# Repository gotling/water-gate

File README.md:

# Watergate

A growhose helper. Sensors and watering of plants with added nutrition. 

# Configuration

WiFi config set using WiFi Manager by connecting to network Watergate on first boot.

**gmtOffset_sec**

Adjustment in seconds from GMT

**waterHour**

Array of hours when automatic watering should be done

## MQTT

Setup to use Adafruit IO service.

Configure username, password and topic by creating a *config.h* file with the following defines:

    #define MQTT_USER ""
    #define MQTT_PASSWORD ""
    #define MQTT_TOPIC ""

# Hardware

ESP32 devkit.

DHT22 temperature and humidity sensor.

12v AGM battery.

12v 5w water pump.

Hygrometers for measuring soil humidity.

Buck converter for getting 5v from 12v battery.

Simple voltage divider for checking battery level.

MOSFETs for controlling pump, motor and sensors.

Water level sensors.

# Schematics

First time using KiCad to help with construction.

# Software

Written in Arduino IDE 2.0.

Coded in C.

# Enclosures

Made in Fusion 360 with main purpouse to protect electronics from direct sunligt.

https://a360.co/3csUwN7

# Libraries

These libraries needs to be installed in Arduino IDE to be able to build.

**FTDebouncer** by Ubi de Feo

https://github.com/ubidefeo/FTDebouncer

**DHT sensor library** by Adafruit

https://github.com/adafruit/DHT-sensor-library

**WiFiManager** by tzapu

https://github.com/tzapu/WiFiManager

**PubSubClient** by Nick O'Leary

https://github.com/knolleary/pubsubclient

**DallasTemperature** by Miles Burton

https://github.com/milesburton/Arduino-Temperature-Control-Library

**OneWire** by Jim Studt, ...

https://www.pjrc.com/teensy/td_libs_OneWire.html

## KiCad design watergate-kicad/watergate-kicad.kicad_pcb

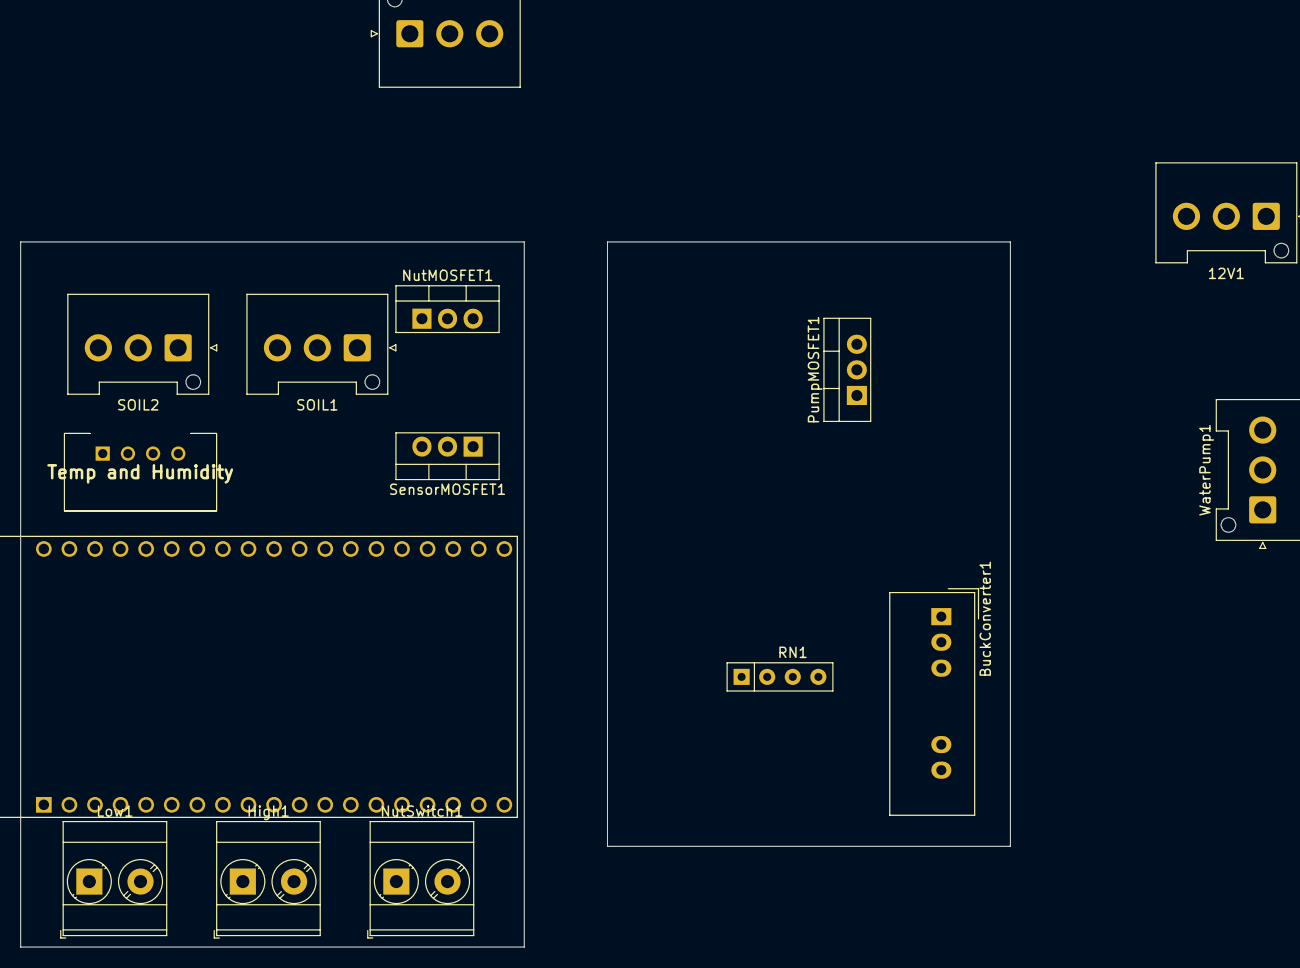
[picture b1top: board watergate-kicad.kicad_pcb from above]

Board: 2 copper layers, 98.3 x 70.0 mm, 15 parts (0 on the bottom side), 18 nets, no tracks yet.

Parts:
12V1: Battery; JST_VH_B3P-VH-FB-B_1x03_P3.96mm_Vertical
BuckConverter1: DC12V-DC5V; Converter_DCDC_Murata_NCS1SxxxxSC_THT
High1: WaterLevelSwitch; TerminalBlock_Phoenix_MKDS-3-2-5.08_1x02_P5.08mm_Horizontal
Low1: WaterLevelSwitch; TerminalBlock_Phoenix_MKDS-3-2-5.08_1x02_P5.08mm_Horizontal
NutMOSFET1: IRLZ34N; TO-220-3_Vertical
NutMotor1: Motor_DC; JST_VH_B3P-VH-FB-B_1x03_P3.96mm_Vertical
NutSwitch1: Switch; TerminalBlock_Phoenix_MKDS-3-2-5.08_1x02_P5.08mm_Horizontal
PumpMOSFET1: IRLZ34N; TO-220-3_Vertical
RN1: VoltageDivider; R_Array_SIP4
SOIL1, SOIL2: Soil_Measure_Analog; JST_VH_B3P-VH-FB-B_1x03_P3.96mm_Vertical
SensorMOSFET1: IRLZ34N; TO-220-3_Vertical
Temp and Humidity: DHT22
U1: ESP32-DEVKITC-32D; MODULE_ESP32-DEVKITC-32D
WaterPump1: Motor_DC; JST_VH_B3P-VH-FB-B_1x03_P3.96mm_Vertical

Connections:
unnamed: 12V1.1 (+), BuckConverter1.2 (+VIN), RN1.3, WaterPump1.1 (+)
unnamed: 12V1.2 (-), BuckConverter1.1 (-VIN), NutMOSFET1.2 (D), PumpMOSFET1.2 (D), RN1.1, U1.14 (GND1)
unnamed: High1.1, Low1.1, NutSwitch1.1, Temp and Humidity.1 (VDD), U1.1 (3V3)
unnamed: NutMOSFET1.1 (G), NutMotor1.2 (-)
unnamed: NutMOSFET1.3 (S), U1.13 (IO12)
unnamed: BuckConverter1.6 (+VOUT), NutMotor1.1 (+), SOIL1.2 (VCC), SOIL2.2 (VCC), U1.19 (EXT_5V)
unnamed: PumpMOSFET1.1 (G), WaterPump1.2 (-)
unnamed: PumpMOSFET1.3 (S), U1.12 (IO14)
unnamed: SOIL1.1 (GND), SOIL2.1 (GND), SensorMOSFET1.1 (G)
unnamed: SOIL1.3 (AUOT), U1.31 (IO16)
unnamed: SOIL2.3 (AUOT), U1.32 (IO4)
unnamed: SensorMOSFET1.2 (D), Temp and Humidity.4 (GND), U1.20 (GND3)
unnamed: SensorMOSFET1.3 (S), U1.33 (IO0)
unnamed: High1.2, U1.9 (IO25)
unnamed: Low1.2, U1.10 (IO26)
unnamed: NutSwitch1.2, U1.11 (IO27)
unnamed: RN1.2, U1.15 (IO13)
unnamed: Temp and Humidity.2 (DATA), U1.21 (IO23)

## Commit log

2022-06-16 Add liquid level sensors
2022-06-16 Add 3 hygrometer sensors and one temperature probe
2022-06-30 Read battery voltage
2022-06-30 Wiring hints
2022-06-30 Add nutrition until target
2022-06-30 Button and LED form manual control
2022-07-15 MQTT, automation
2022-07-18 Debug logging
2022-07-18 Rename event
2022-07-18 Move pin arounds to handle ADC2 unavailable using WiFi
2022-07-18 Avoid logging invalid data from soil temp probe
2022-07-18 Schedule watering using time from NTP
2022-07-18 Turn off WiFi before sleep
2022-07-18 Helper state
2022-07-18 Turn off if emptying takes to long
2022-07-18 Handle manual wakeup
2022-07-22 Documentation
2022-07-22 Update to reality
2022-07-24 Start refactoring code. Break out sensor functions
2022-07-24 Extract voltage
2022-07-24 Sensor loop
2022-07-24 Sleep and time
2022-08-07 Read level as part of reading sensors
2022-08-07 Fail WiFi connection after 30 seconds
2022-08-07 Relating to level
2022-08-07 Separate log and led to separate file
2024-04-19 Change WiFi connect/disconnect, average sensor readings, use external RTC
2024-07-28 Schedule adding nutrition
